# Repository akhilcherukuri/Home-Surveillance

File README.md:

# Home-Surveillance
BE Third Year Electronics and Communication Engineering Project

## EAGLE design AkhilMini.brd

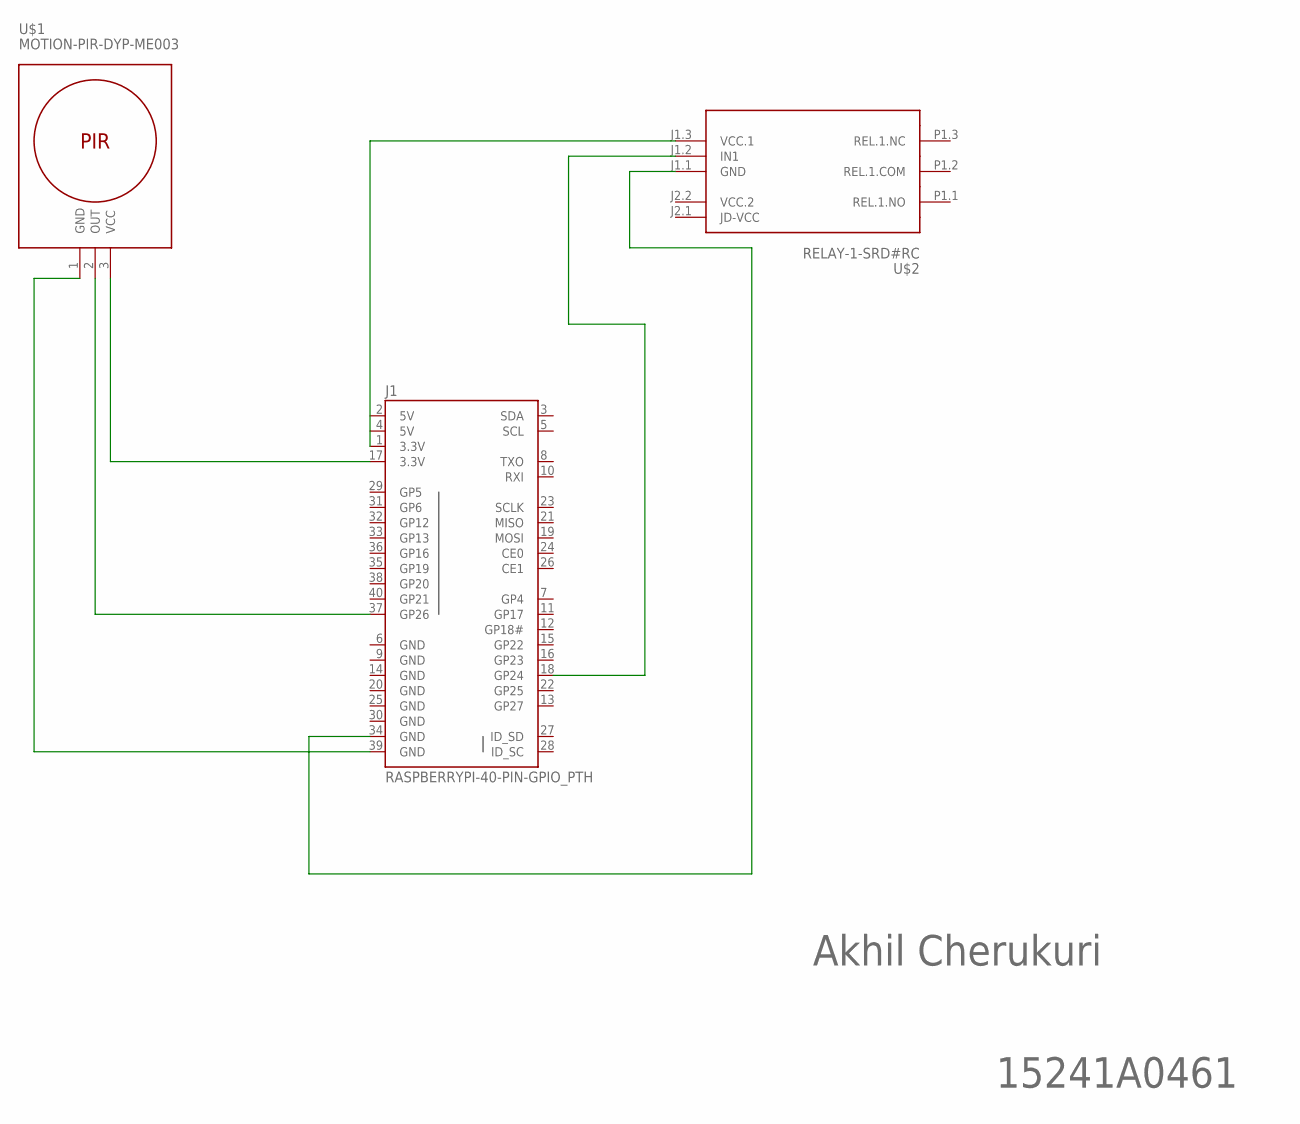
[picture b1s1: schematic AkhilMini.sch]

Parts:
J1: RASPBERRYPI-40-PIN-GPIO_PTH; 2X20_SHROUDED
U$1: MOTION-PIR-DYP-ME003
U$2: RELAY-1-SRD#RC

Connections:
5V: J1.2 (5V), J1.4 (5V)
GND: J1.6 (GND), J1.9 (GND), J1.14 (GND), J1.20 (GND), J1.25 (GND), J1.30 (GND)
unnamed: J1.17 (3.3V), U$1.3 (VCC)
unnamed: J1.1 (3.3V), U$2.J1.3 (VCC.1)
unnamed: J1.34 (GND), U$2.J1.1 (GND)
unnamed: J1.39 (GND), U$1.1 (GND)
unnamed: J1.37 (GP26), U$1.2 (OUT)
unnamed: J1.18 (GP24), U$2.J1.2 (IN1)
VCC.2: U$2.J2.2 (VCC.2)

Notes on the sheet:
Akhil Cherukuri
15241A0461

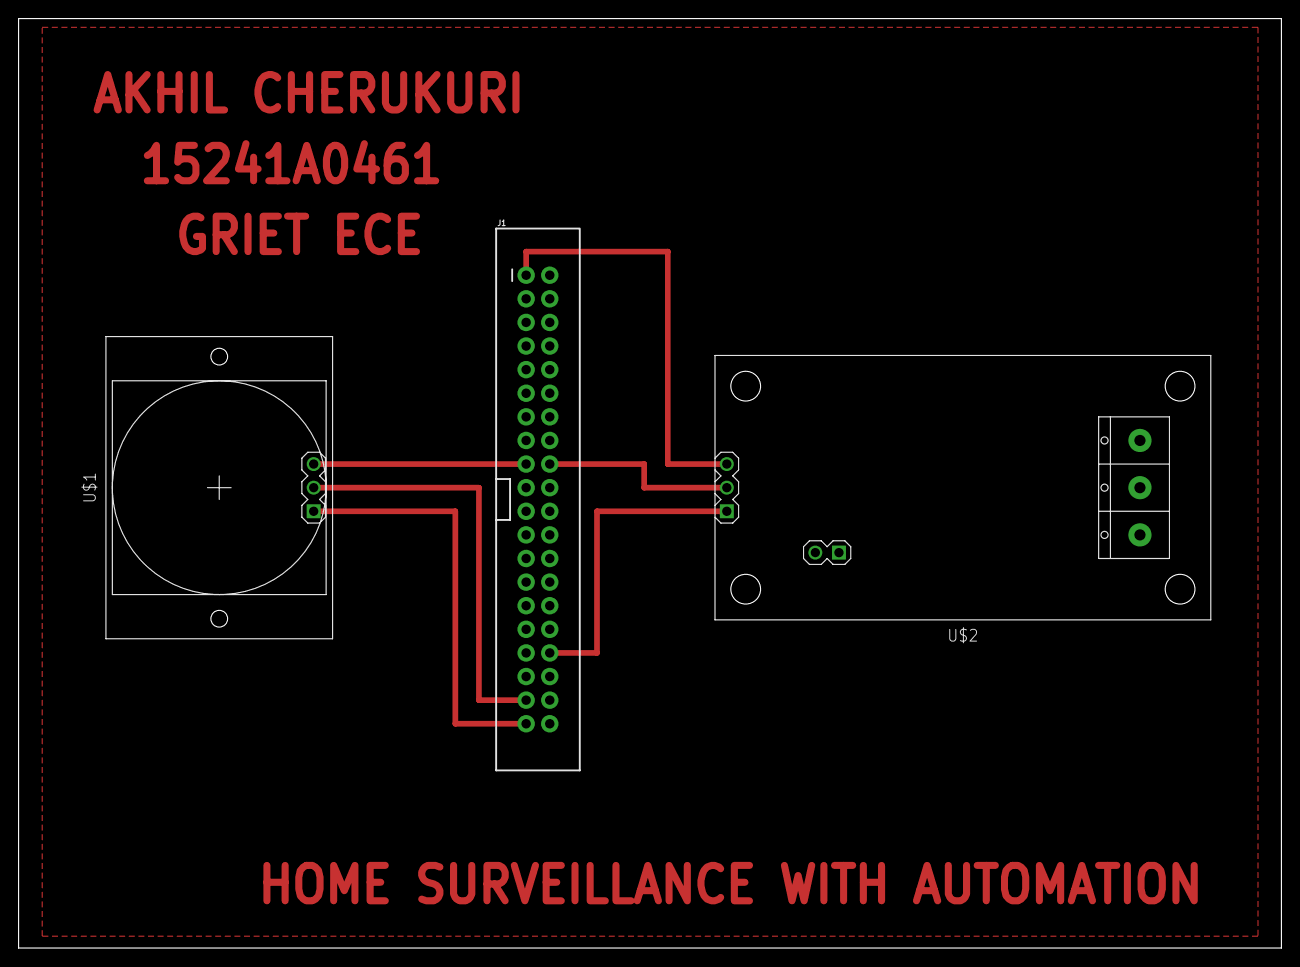
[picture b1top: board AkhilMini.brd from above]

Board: 2 copper layers, 135.9 x 100.0 mm, 3 parts (0 on the bottom side), 8 nets.

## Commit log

2020-10-09 Commit 2

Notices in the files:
parts and their libraries:
SparkFun-Connectors: Licensing: Creative Commons ShareAlike 4.0 International - https://creativecommons.org/licenses/by-sa/4.0
diy-modules: Released under the Creative Commons Attribution 4.0 International License: http://creativecommons.org/licenses/by/4.0
